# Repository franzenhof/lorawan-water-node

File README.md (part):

# LoRaWAN Water Node – Spring & Reservoir Monitor (Heltec WiFi LoRa V3)

Firmware for a custom-built PCB based on the **Heltec WiFi LoRa 32 V3** (ESP32-S3).  
The node measures flow rate, water level, and process temperatures at a natural spring or water reservoir, and transmits all data via **LoRaWAN (OTAA, region configurable; default: EU868)** to a ChirpStack server. The BME280 values are used mainly for enclosure health monitoring (humidity ingress + electronics thermal state), not as a primary water-process sensor.

---

## Project Photos

<p align="center">
     <sub><strong>Overview:</strong> Complete field setup</sub><br/>
     <sub><strong>PCB Prototype:</strong> Board and wiring stage (Fritzing prototype)</sub><br/>
     <sub><strong>Grafana:</strong> Live telemetry and trends</sub>
</p>

<p align="center">

     <br/>
     
</p>

<p align="center">
     <sub><strong>PCB v1.0 (KiCad render):</strong> top side with Heltec module footprint, bottom side with terminal labels, 3D view</sub>
</p>

---

## Quick Navigation

- [Use Case](#use-case)
- [Operating Modes & Display](#operating-modes--display)
- [Hardware](#hardware) · [PCB v1.0](#pcb-v10) · [Prototype](#prototype-fritzing)
- [GPIO Pinout](#gpio-pinout)
- [CayenneLPP Payload](#cayennelpp-payload-channels) · [Payload Format](#payload-format-cayennelpp-or-compact-binary) · [Daily Uplink](#daily-uplink-port-2)
- [Building & Flashing](#building--flashing) · [Tests](#tests)
- [Initial Configuration](#initial-configuration-wifi-portal)
- [User Button](#user-button-gpio-0)
- [Firmware Update (OTA)](#firmware-update-via-wi-fi-portal-ota)
- [LoRaWAN Session & Join](#lorawan-session--join)
- [TTN Instead of ChirpStack](#ttn-the-things-stack-instead-of-private-chirpstack)
- [Downlink Commands](#downlink-commands)
- [4–20 mA Measurement](#420-ma-current-measurement)
- [Power Saving](#power-saving-measures) · [Power Consumption](#power-consumption)
- [Libraries](#libraries)
- [ChirpStack Decoder](#chirpstack-decoder)
- [Troubleshooting](#troubleshooting)
- [Project Structure](#project-structure)
- [Changelog](#changelog)

---

## 📄 License & Open Source

This project is fully open-source. To support both software developers and hardware makers, it is dual-licensed:

* **Software / Firmware:** Licensed under the **[MIT License](LICENSE-SOFTWARE)**. You can freely use, modify, and distribute the code.
* **Hardware (Schematics, PCB & 3D Files):** Licensed under the **[CERN-OHL-P v2](LICENSE-HARDWARE)** (CERN Open Hardware Licence – Permissive). You are free to manufacture, modify, and distribute the hardware designs.

*Developed with 🚜 and 💻 by Gerhard Massenbichler at Franzenhof.*

## Use Case

```
[LiFePO4 4s] ──► [Victron MPPT] ──► charge battery
                                         │
                              [DALY Smart BMS] (protection)
                                         │ 12 V (VIN 6–33 V)
                              [Water Node PCB v1.0]
                               on-board VIN → 5 V buck, 5 V → 22 V boost
                                         │
                              [Heltec WiFi LoRa V3]
                                    │        │
               [Flow sensor, e.g. ZJ-B5]   [DS18B20 x3]
                          [4-20mA Level]   [BME280 enclosure monitor]
                          [Victron VE.Direct]
                          [DALY BMS UART]
                                    │
                               [LoRaWAN]
                                    │
                            [ChirpStack Server]
```

Every 5 minutes the node wakes from deep sleep, samples for up to 15 seconds (averaging), and sends a LoRaWAN uplink. It then returns to deep sleep. The DALY BMS is read less frequently (configurable interval, default every 6th cycle = 30 minutes).

---

## Operating Modes & Display

**Deep-sleep mode (`sleepSec > 0`, default):** wake, measure for the sampling window, send, sleep. The window ends early (after at least 5 s) once Victron and DALY have answered. The flow sensor is unpowered while sleeping, so the flow *rate* is measured during the window only.

**Continuous mode (`sleepSec = 0`):** deep sleep is disabled. The node stays awake, samples continuously over the continuous uplink interval, forms window averages, and sends at that interval. Flow, 4–20 mA level, DS18B20, BME280, and Victron V/P/I are averaged across the whole window. Flow pulses are captured without gaps (including during uplink/processing phases), so no liters are lost between cycles.
> **Note:** In continuous mode, the sampling window (`samplingMs`) is ignored — the measurement window is governed solely by the continuous interval (`continuousSendSec`).

**Display power management (automatic, no configuration needed in deep-sleep mode):**
- **Deep sleep (`sleepSec>0`):** the display is **off** on a normal timer wakeup (silent, unattended cycle), and automatically turned **on** for a fresh power-on boot or an EXT0 button wakeup — staying on until the measurement is done and the uplink has been sent, then switching off again before the next deep sleep. This is fixed behavior and not user-configurable, since keeping the display on during unattended timer cycles would only waste battery power for no benefit.
- **Continuous mode (`sleepSec=0`):** since the node never deep-sleeps, there is no wakeup event to hook into. Instead, the display stays on for `displayOnCycles` measurement cycles (configurable, default 5; **`0` = always on, no auto-off**) after boot or after a **short press** of the user button (GPIO 0), then turns off automatically until the button is pressed again. A short press is recognized even while a (potentially long) measurement window is running, so the display reacts immediately rather than waiting for the next full cycle.

If the display is on, it doesn't just show a static "Measuring..." message: it updates once per second during the whole measurement window with a countdown, the running flow rate, the running 4–20 mA level average, Victron/DALY BMS reception status (`...` while waiting, `OK` once received), and — in continuous mode — the live DS18B20 temperatures. To keep the ~750 ms 12-bit conversion from stalling the ADC/serial sampling, the DS18B20 are read **asynchronously** in continuous mode (a fresh conversion is started right after each read). At uplink time, the continuous-mode payload uses the window averages (instead of last-sample values) for flow, level, DS18B20, BME280, and Victron V/P/I. In deep-sleep mode the sensors are read once (blocking) after the short measurement window to save power. So the user always sees live feedback instead of a frozen screen.

All measurement screens (live "Measuring…", the final results screen, and the "Sending uplink…" screen) list values in a fixed **priority order (most important first): Flow → DS18B20 temperatures → Level → BME280 → Victron → DALY → rest (VIN, inputs/outputs)**. Lines are drawn compactly (only present sensors); on the 64 px panel the lowest-priority values drop off the bottom first if everything is enabled at once. The "Sending uplink…" screen keeps the measured values visible under the header instead of blanking the screen. If known and `debugMode = 1`, RF quality values (last downlink RSSI/SNR and LinkCheck results) are shown as commissioning info. When the display is off, the node does not wait at the end of the cycle (the 4 s result screen is only shown with the display on).

---

## Hardware

The hardware is **PCB v1.0** (KiCad, SMD, JLCPCB-ready) in [`pcb/v1.0/`](pcb/v1.0/). The original Fritzing board (THT, external DC-DC converters) is kept as the [prototype](#prototype-fritzing) in [`pcb/prototype/`](pcb/prototype/); the current firmware no longer supports it.

| Component | Function |
|-----------|----------|
| Heltec WiFi LoRa 32 V3 | Microcontroller (ESP32-S3), LoRa SX1262 — plugs onto the PCB (2 × 18-pin sockets), USB-C at the board edge |
| Flow sensor (open collector) | any flow sensor with open-collector output (e.g. ZJ-B5) |
| DS18B20 × 3 | 1-Wire temperature sensors (spring, tank floor, air) |
| BME280 | Enclosure health monitoring: humidity ingress indicator, enclosure/electronics temperature trend, plus barometric pressure as an additional byproduct value (I²C) |
| 4–20 mA level sensor | Two-wire loop sensor, supplied with 22 V by the on-board boost converter |
| Victron MPPT | Solar charge controller, read via VE.Direct (serial) |
| DALY Smart BMS | Battery protection, read via UART |

### PCB v1.0

**Board:** 100 × 100 mm, 2 layers, 4 × M3 mounting holes (4 mm from the edges → **92 × 80 mm** hole pattern; the lower pair sits above the terminal row). The field connectors are 3.5 mm screw terminals along the bottom edge; the I/O block (switched outputs, digital and analog inputs) sits at the top edge. The Heltec module (WiFi LoRa 32 **V3.2**, pin-compatible with V3/V3.1) plugs in at the left edge; its USB-C connector sits 1.5 mm inside the board edge (it does not protrude — updates normally go over the air). Board version and `franzenhof.com` are printed on both sides. The top silkscreen names every terminal block **and each of its pins** right at the terminal, so the board can be wired when it is mounted; it also documents the jumpers and headers. The bottom silkscreen repeats the pin names.

**RTC pin map:** every input, pulse input and output sits on an RTC GPIO (GPIO1–7, GPIO19). Inputs can therefore wake the ESP32-S3 from deep sleep (once JP9 / JP10 keep their input stage powered), and the outputs are held per pin through deep sleep.

**Power:** a single input **VIN 6–33 V** feeds everything — 4s/8s LiFePO4, 12 V / 24 V lead-acid (also 12s with equalization ≤ 33 V), 12 V or 24 V power supplies (24 V PLC supplies per IEC 61131-2):

| Block | Parts | Notes |
|---|---|---|
| Input protection | PTC F1 (1.1 A, 60 V) → bidirectional TVS **SMBJ33CA** → reverse-polarity diode SS210 (100 V) | reverse polarity is blocked by SS210 (electronics) and Q12 (outputs); the bidirectional TVS stays off, so nothing has to blow (a battery would drive far more than F1's 40 A rating into a unidirectional TVS) |
| VIN → 5 V | TI **LMR36510** synchronous buck (4.2–65 V, 1 A, 26 µA Iq) → jumper **JP8** → 5 V rail | supplies the Heltec 5 V pin |
| 5 V → 22 V | **MT3608** boost (22.2 V, below the 24 V standoff of TVS D8 with feedback tolerance), input switched by P-MOSFET AO3401A (GPIO47) | 4–20 mA loop supply, independent of VIN (also on USB power); completely off in deep sleep |
| 3.3 V | own LDO **XC6206P332MR** (U15, 200 mA, ≈ 1 µA Iq) from the 5 V rail via PTC F2; switched sensor rail via **AO3401A** (GPIO38) | the Heltec 3V3 regulator only supplies the module; the switched rail also powers the whole I²C domain (BME280, ADS1115, J16) |
| 5 V sensor rail | AO3400A + AO3401A, enabled together with the 3.3 V sensor rail | pulse sensors |
| Output load supply | own branch: VIN terminal → reverse-polarity P-MOSFET **NCE60P50K** (Q12, 60 V, 28 mΩ; D37 12 V gate clamp, R63 1 MΩ) → **eFuse TPS16630** (U16, 60 V, 31 mΩ) → J17 "+VIN" | loads run at the VIN voltage and do not stress the electronics' input fuse; no diode drop or diode heat at 3 A. U16 limits the total load current to **5.4 A** (R64 3.3k; the datasheet allows 0.6–6 A, R_ILIM ≥ 3 kΩ), so pumps and motors with a start current of up to 5.4 A start normally; above that it holds the current for at most 162 ms (less if it reaches thermal shutdown), switches off and retries every 0.65 s. On a hard short (at an output or at +VIN) it switches off within ~1 µs. The continuous rating stays 3 A in total; the eFuse protects against shorts and stalled motors, not against a moderate continuous overload between 3 and 5.4 A. It is only enabled while at least one output is on (SHDN = diode OR of the three output GPIOs, D38/D39 + R65): 21 µA with all outputs off, 1.4 mA while an output is on |

> **USB-only bench test / flashing:** remove jumper **JP8** ("5V BUCK", note printed on the bottom side). The board then runs from the Heltec USB-C port alone (ESP32, LoRa, display, sensors, inputs, ADS1115, 4–20 mA loop); only the outputs at J17 need VIN. With JP8 removed the buck converter is not back-fed, and USB and buck never drive the 5 V rail at the same time — Heltec specifies that only one supply (USB *or* 5 V pin) may be connected. Put JP8 back for normal operation.

**Field connectors** (bottom edge, left → right; function and pin names on the top silkscreen, pin names also on the bottom):

| Ref | Connector | Pins |
|---|---|---|
| J3 | VIN 6–33 V | 1 VIN, 2 GND |
| J7 | 4–20 mA level | 1 `+22V` (loop supply), 2 `SIG` (loop return → 120 Ω shunt → ADS1115) |
| J4 | Pulse inputs | 1 OC1 (flow sensor, GPIO5), 2 OC2 (2nd pulse input, GPIO6), 3 +5 V, 4 GND — **OC1/OC2 0–33 V**: open collector / NPN, contacts, 3.3/5 V logic, sensors with an internal 5 V pull-up and 12/24 V push-pull pulse outputs; PNP outputs with JP16 set to pull-down |
| J8 | 1-Wire (DS18B20) | 1 GND, 2 3V3, 3 DQ |
| J9 / J12 | VE.Direct (isolated) | screw terminal: 1 GND, 2 RX (to Victron), 3 TX (from Victron), 4 V+ — wire 1:1 to the Victron socket · **J12** JST-PH 4-pin for the **original (crossed) Victron VE.Direct cable** |
| J10 / J13 | DALY BMS UART (isolated) | 1 GND, 2 3.3 V, 3 BAT (battery voltage from the BMS port, see JP4), 4 S1 (wake-up), 5 TX (from BMS), 6 RX (to BMS) — same order as the DALY UART port · **J13** 6-pin 2.0 mm header for the original DALY cable |

**I/O block** (top edge, left → right):

| Ref | Connector | Pins / function |
|---|---|---|
| J17 | 3 switched outputs | **+VIN \| OUT1 \| OUT2 \| OUT3 \| GND** — low-side switches AON7264E (60 V, 13 mΩ; OUT1 = GPIO19 (Q11), OUT2 = GPIO2 (Q7), OUT3 = GPIO1 (Q6), HIGH = on; gates driven with 5 V by 74AHCT1G125 buffers U14/U13/U12, so the MOSFETs are fully enhanced), load between +VIN and OUTx, **3 A per output, 3 A together continuous**; the load-supply eFuse U16 limits the total to 5.4 A (start currents of pumps / motors) and switches off on a short (auto-retry, all outputs share it), freewheel diodes for valves/pumps/relays; off at reset; the load runs at the VIN voltage (12 V or 24 V loads) |
| J18 | 3 digital + 2 analog inputs | **IN1 \| IN2 \| IN3 \| AI1 \| AI2 \| GND** — IN1–3: −33…+33 V tolerant (also a reversed 24 V source); dry contacts to GND / NPN (100 kΩ pull-up via diode), PNP sensors (100 kΩ pull-down), 3.3/5 V logic or 12/24 V signals — selected per input with JP13–JP15; bidirectional TVS SMAJ33CA, 47 kΩ + clamps, 5 ms debounce, Schmitt trigger → GPIO3 / GPIO4 / GPIO7 (inverted: input high = GPIO low). AI1/AI2: 0–10 V, 100 k / 47 k divider (input resistance 147 kΩ), TVS, clamp → ADS1115 |

**Analog inputs (ADS1115, I²C 0x48):** 16-bit ADC on the switched 3.3 V. AIN0 = VIN (100 k / 10 k divider, switched on with the sensor rail — no current in deep sleep), AIN1 = 4–20 mA shunt, AIN2/AIN3 = AI1/AI2.

**Internal headers and jumpers:**

| Ref | Function |
|---|---|
| J11 | BME280: 1 3V3S (switched), 2 GND, 3 SCL, 4 SDA |
| J16 | expansion (2.54 mm, populated), pin 1 → 8: **VIN, GND, 5V, GND, 3V3S, SDA, SCL, GPIO46** — VIN at the outer end with GND as its only neighbour, 5V between two GND pins; pins 4–7 (GND, 3V3S, SDA, SCL) take a common 4-pin I²C module directly; 3.3 V logic, unprotected |
| TP1–TP6 | test pads (1 mm holes, not populated) next to each rail: GND, VIN, 5V, 3V3, 3V3 switched, 22V loop |
| TP7, TP8 | bare SMD probe pads (top): TP7 `VLD` = load supply +VIN_LOAD behind Q12 and the eFuse U16 (≈ VIN while an output is on), TP8 `3V3B` = second switched 3.3 V rail (I²C / analog / isolators) |
| JP1 / JP2 | I²C pull-ups (two separate 2-pin headers with a free position between them, so a jumper cannot bridge SCL and SDA): JP1 = extra 4.7 kΩ on SCL, JP2 = extra 4.7 kΩ on SDA for long BME280 cables (10 kΩ are always on board) |
| JP3 | DALY isolator supply: 1-2 = 3.3 V from the BMS, 2-3 = on-board 78L33 (3.3 V like the BMS UART) |
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
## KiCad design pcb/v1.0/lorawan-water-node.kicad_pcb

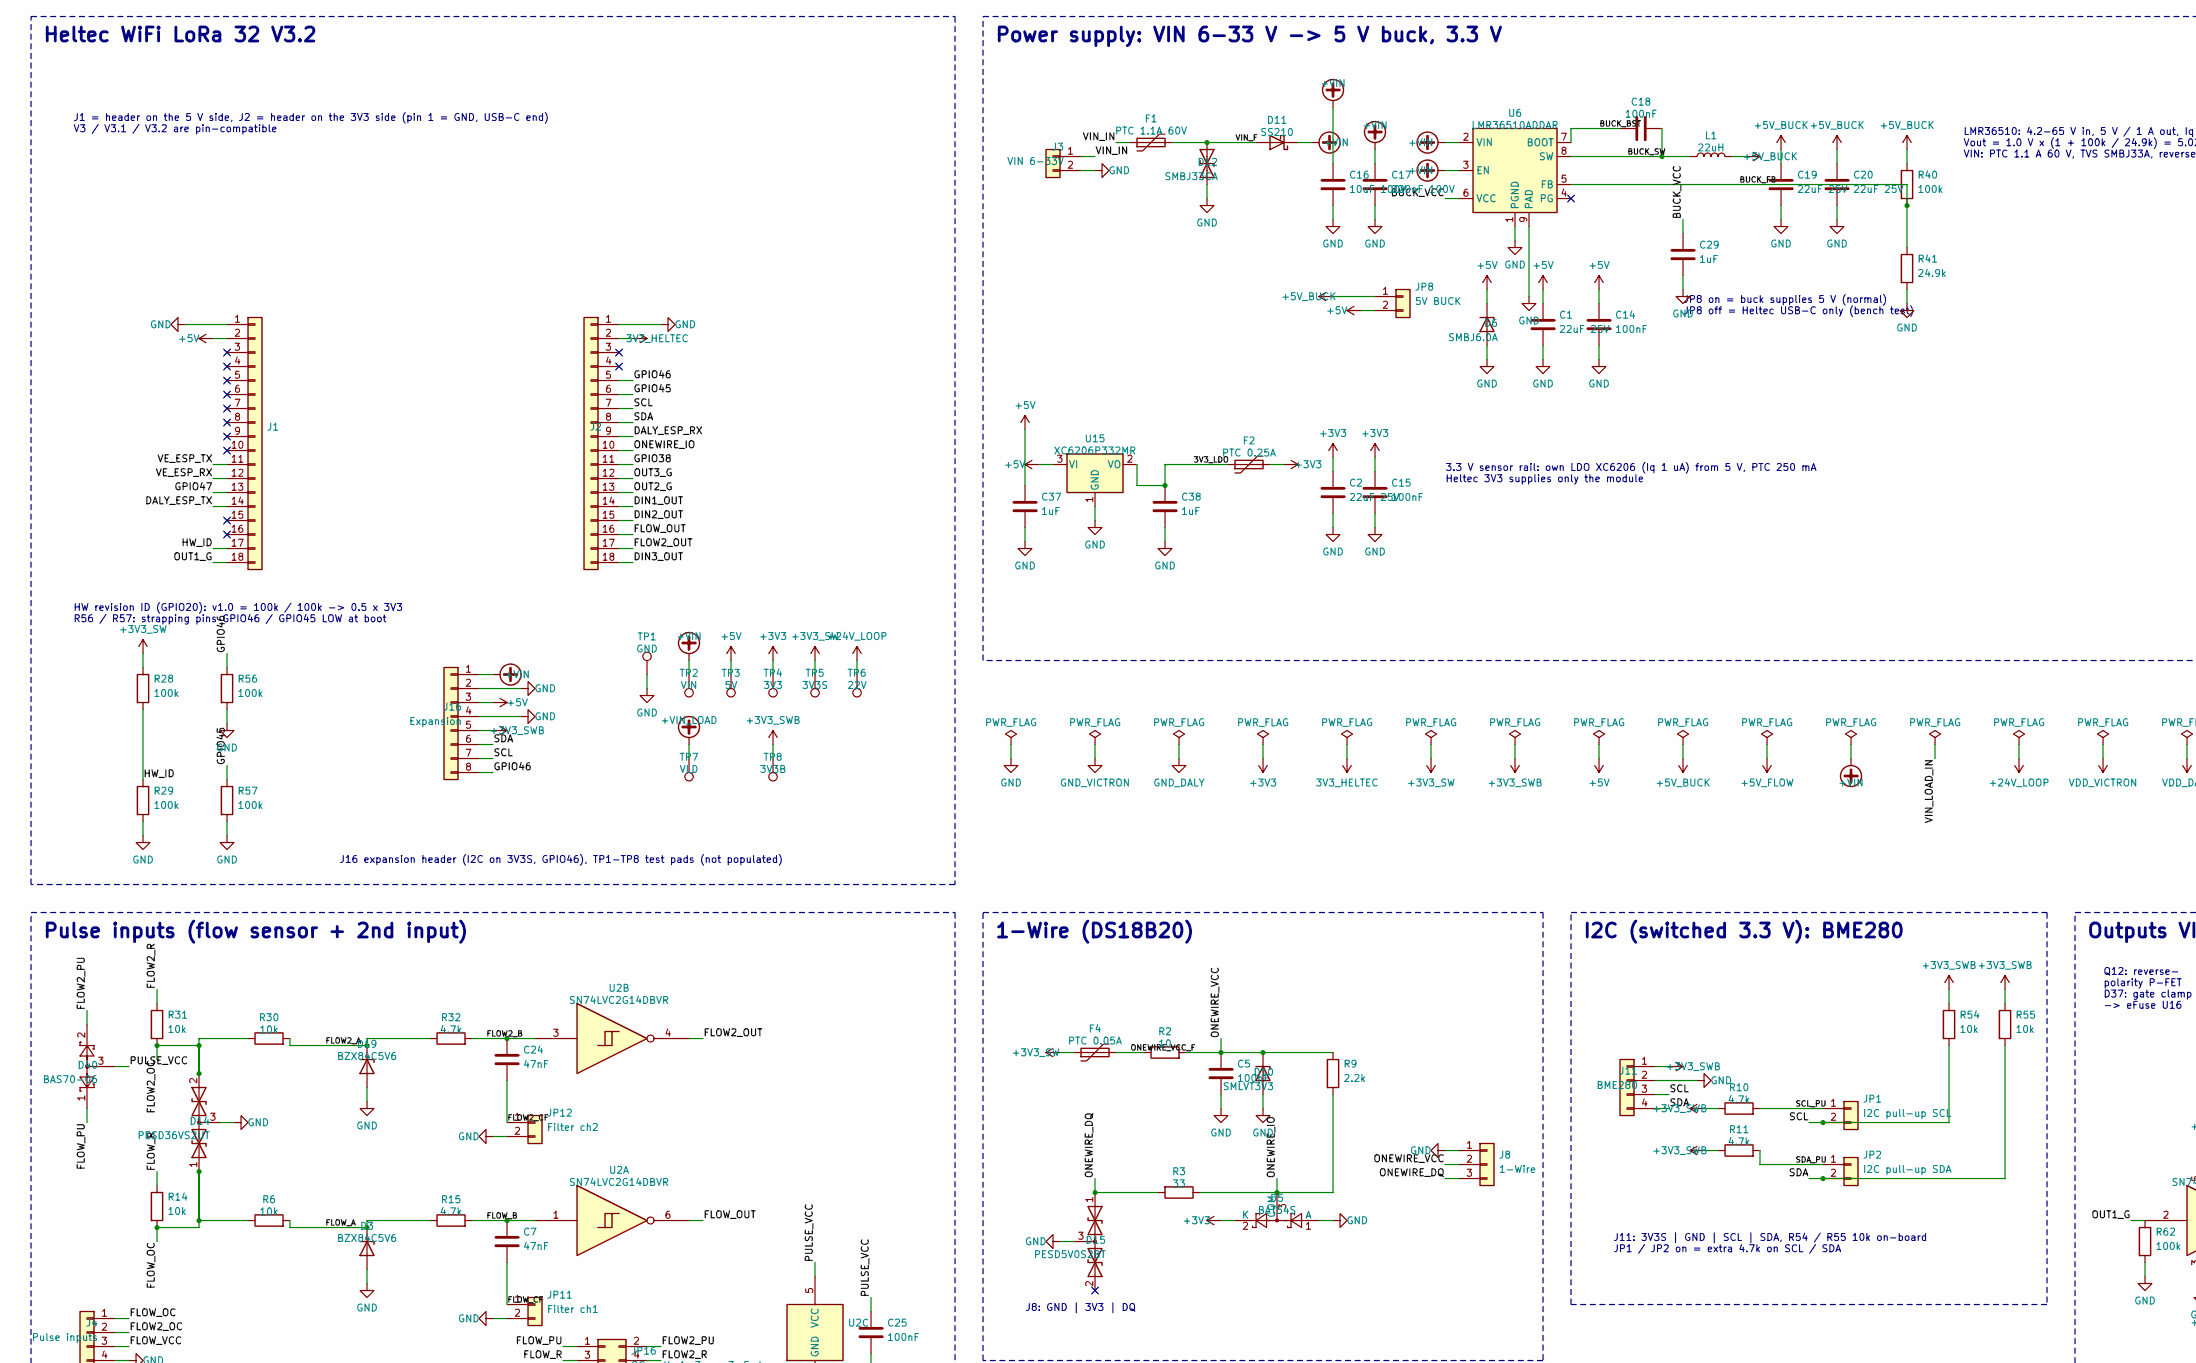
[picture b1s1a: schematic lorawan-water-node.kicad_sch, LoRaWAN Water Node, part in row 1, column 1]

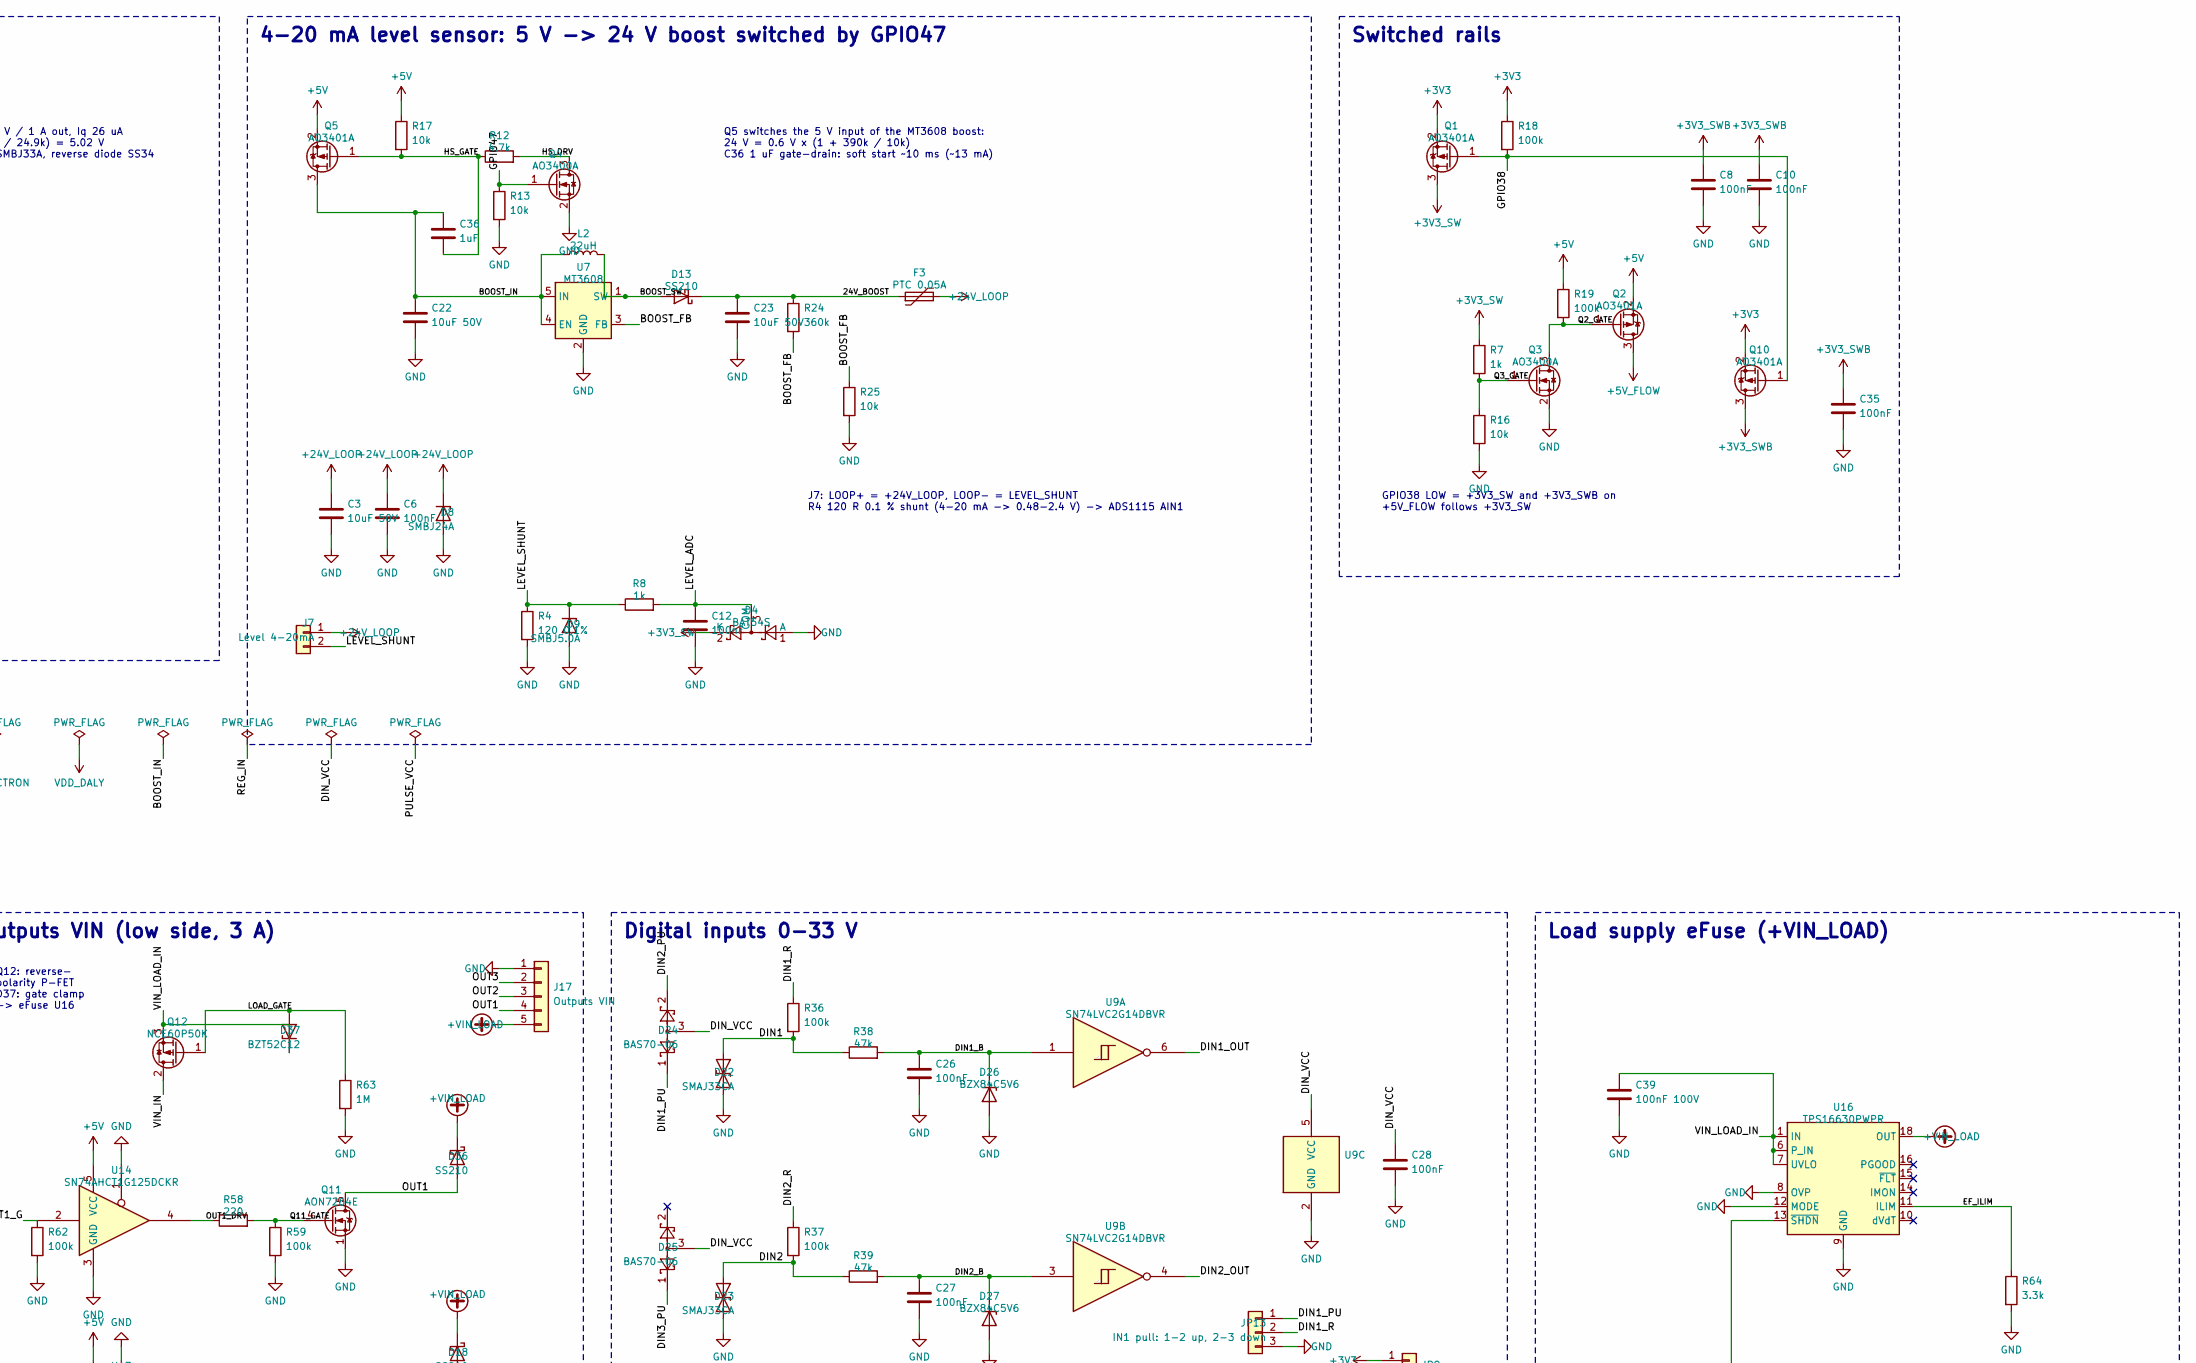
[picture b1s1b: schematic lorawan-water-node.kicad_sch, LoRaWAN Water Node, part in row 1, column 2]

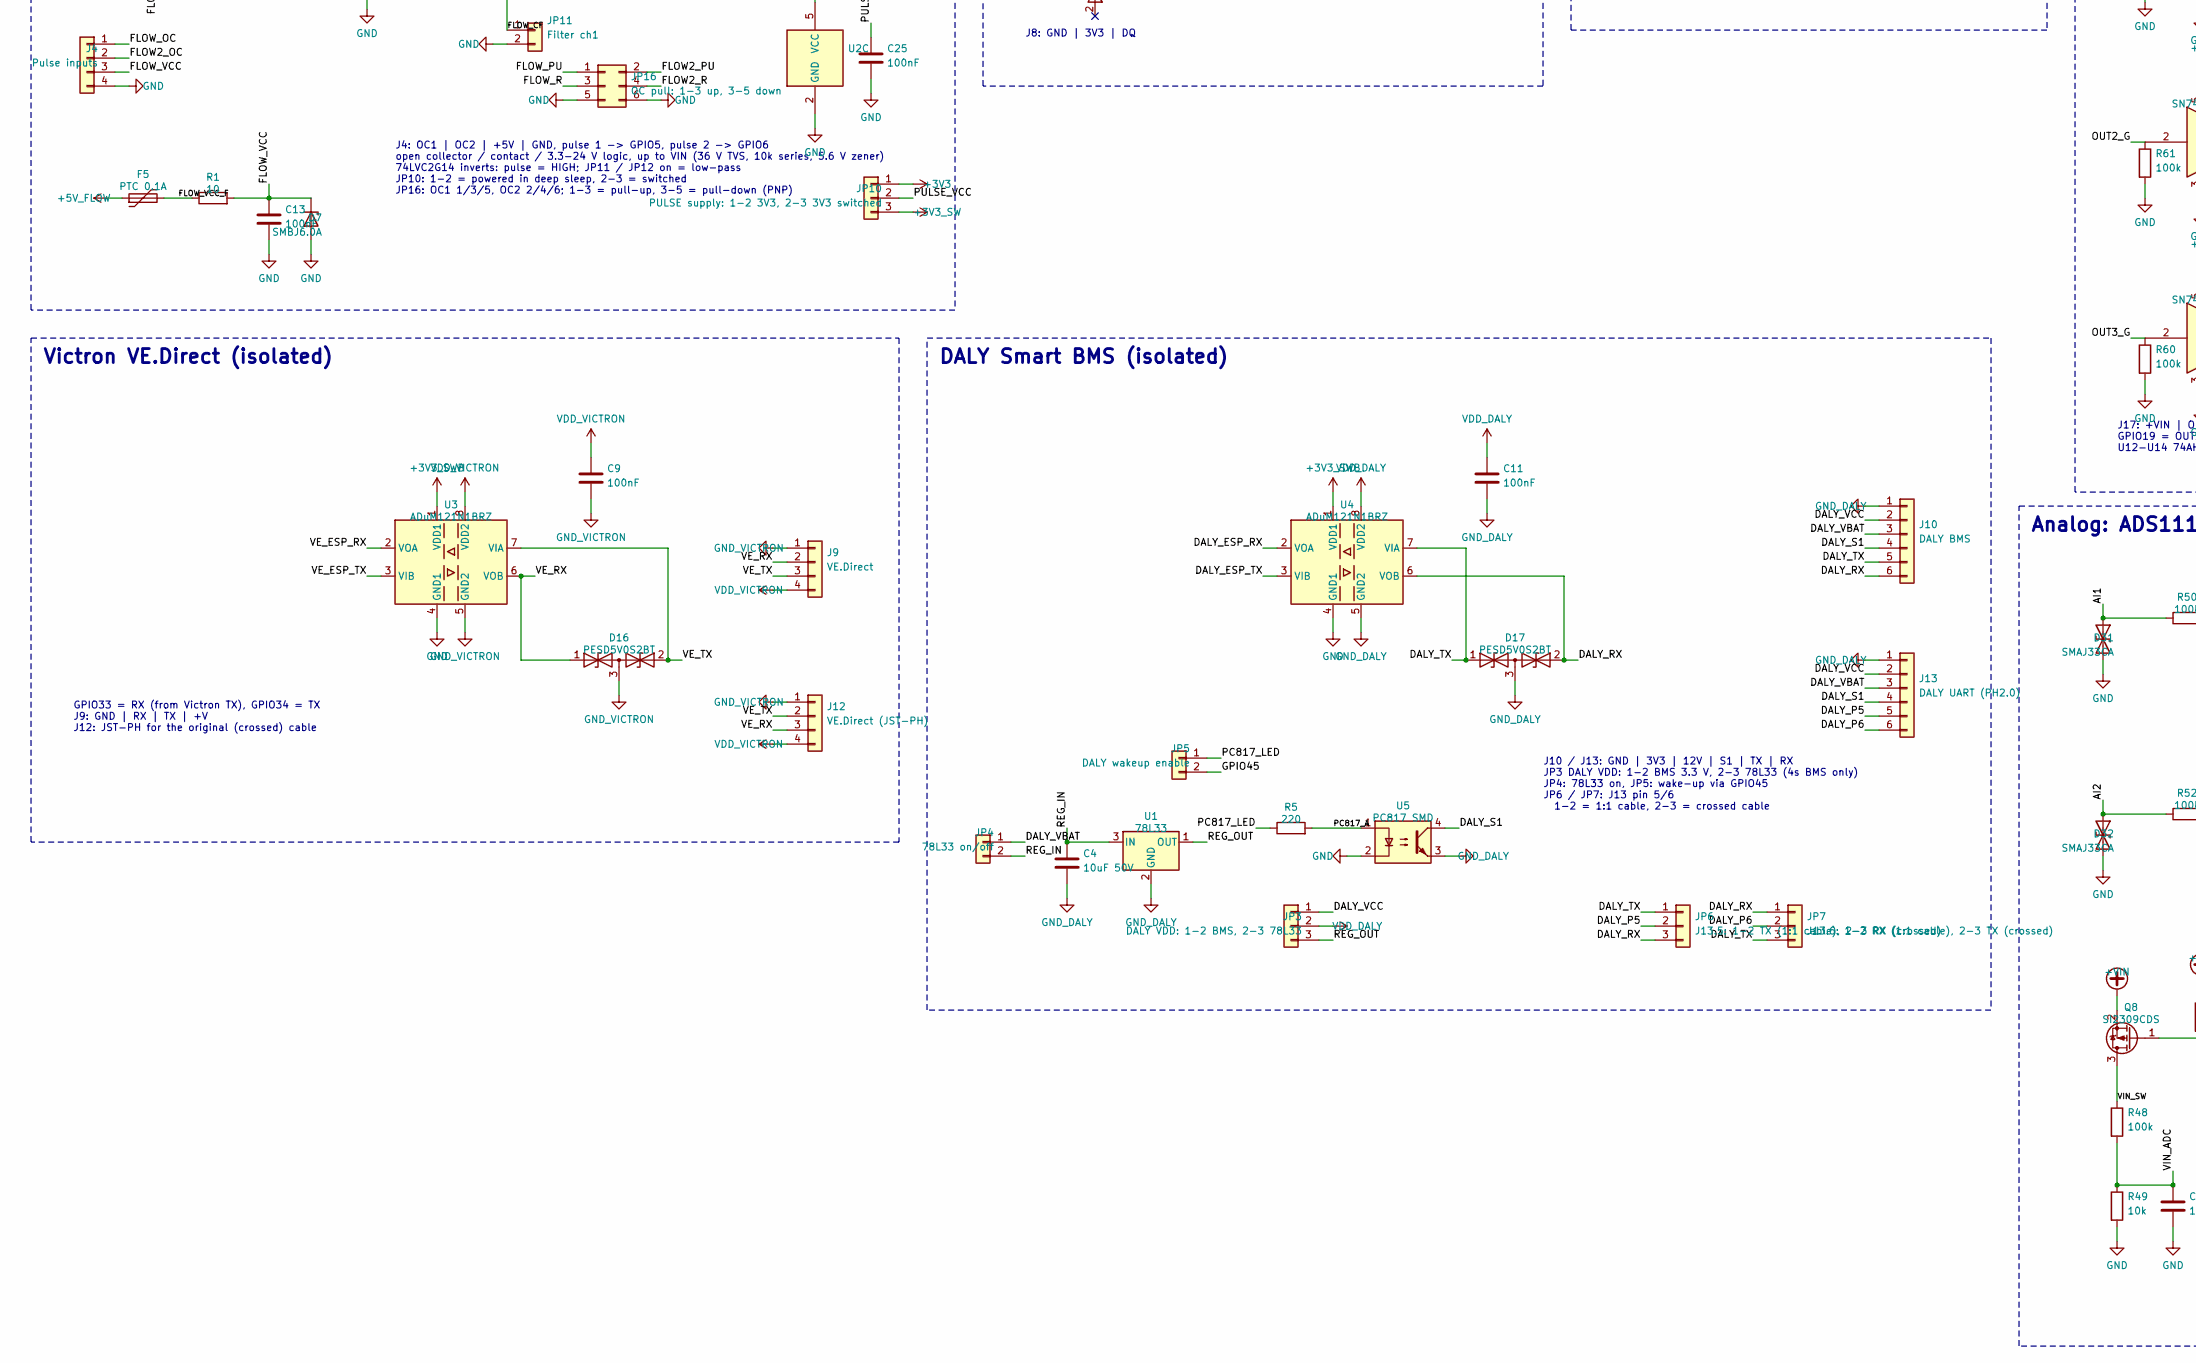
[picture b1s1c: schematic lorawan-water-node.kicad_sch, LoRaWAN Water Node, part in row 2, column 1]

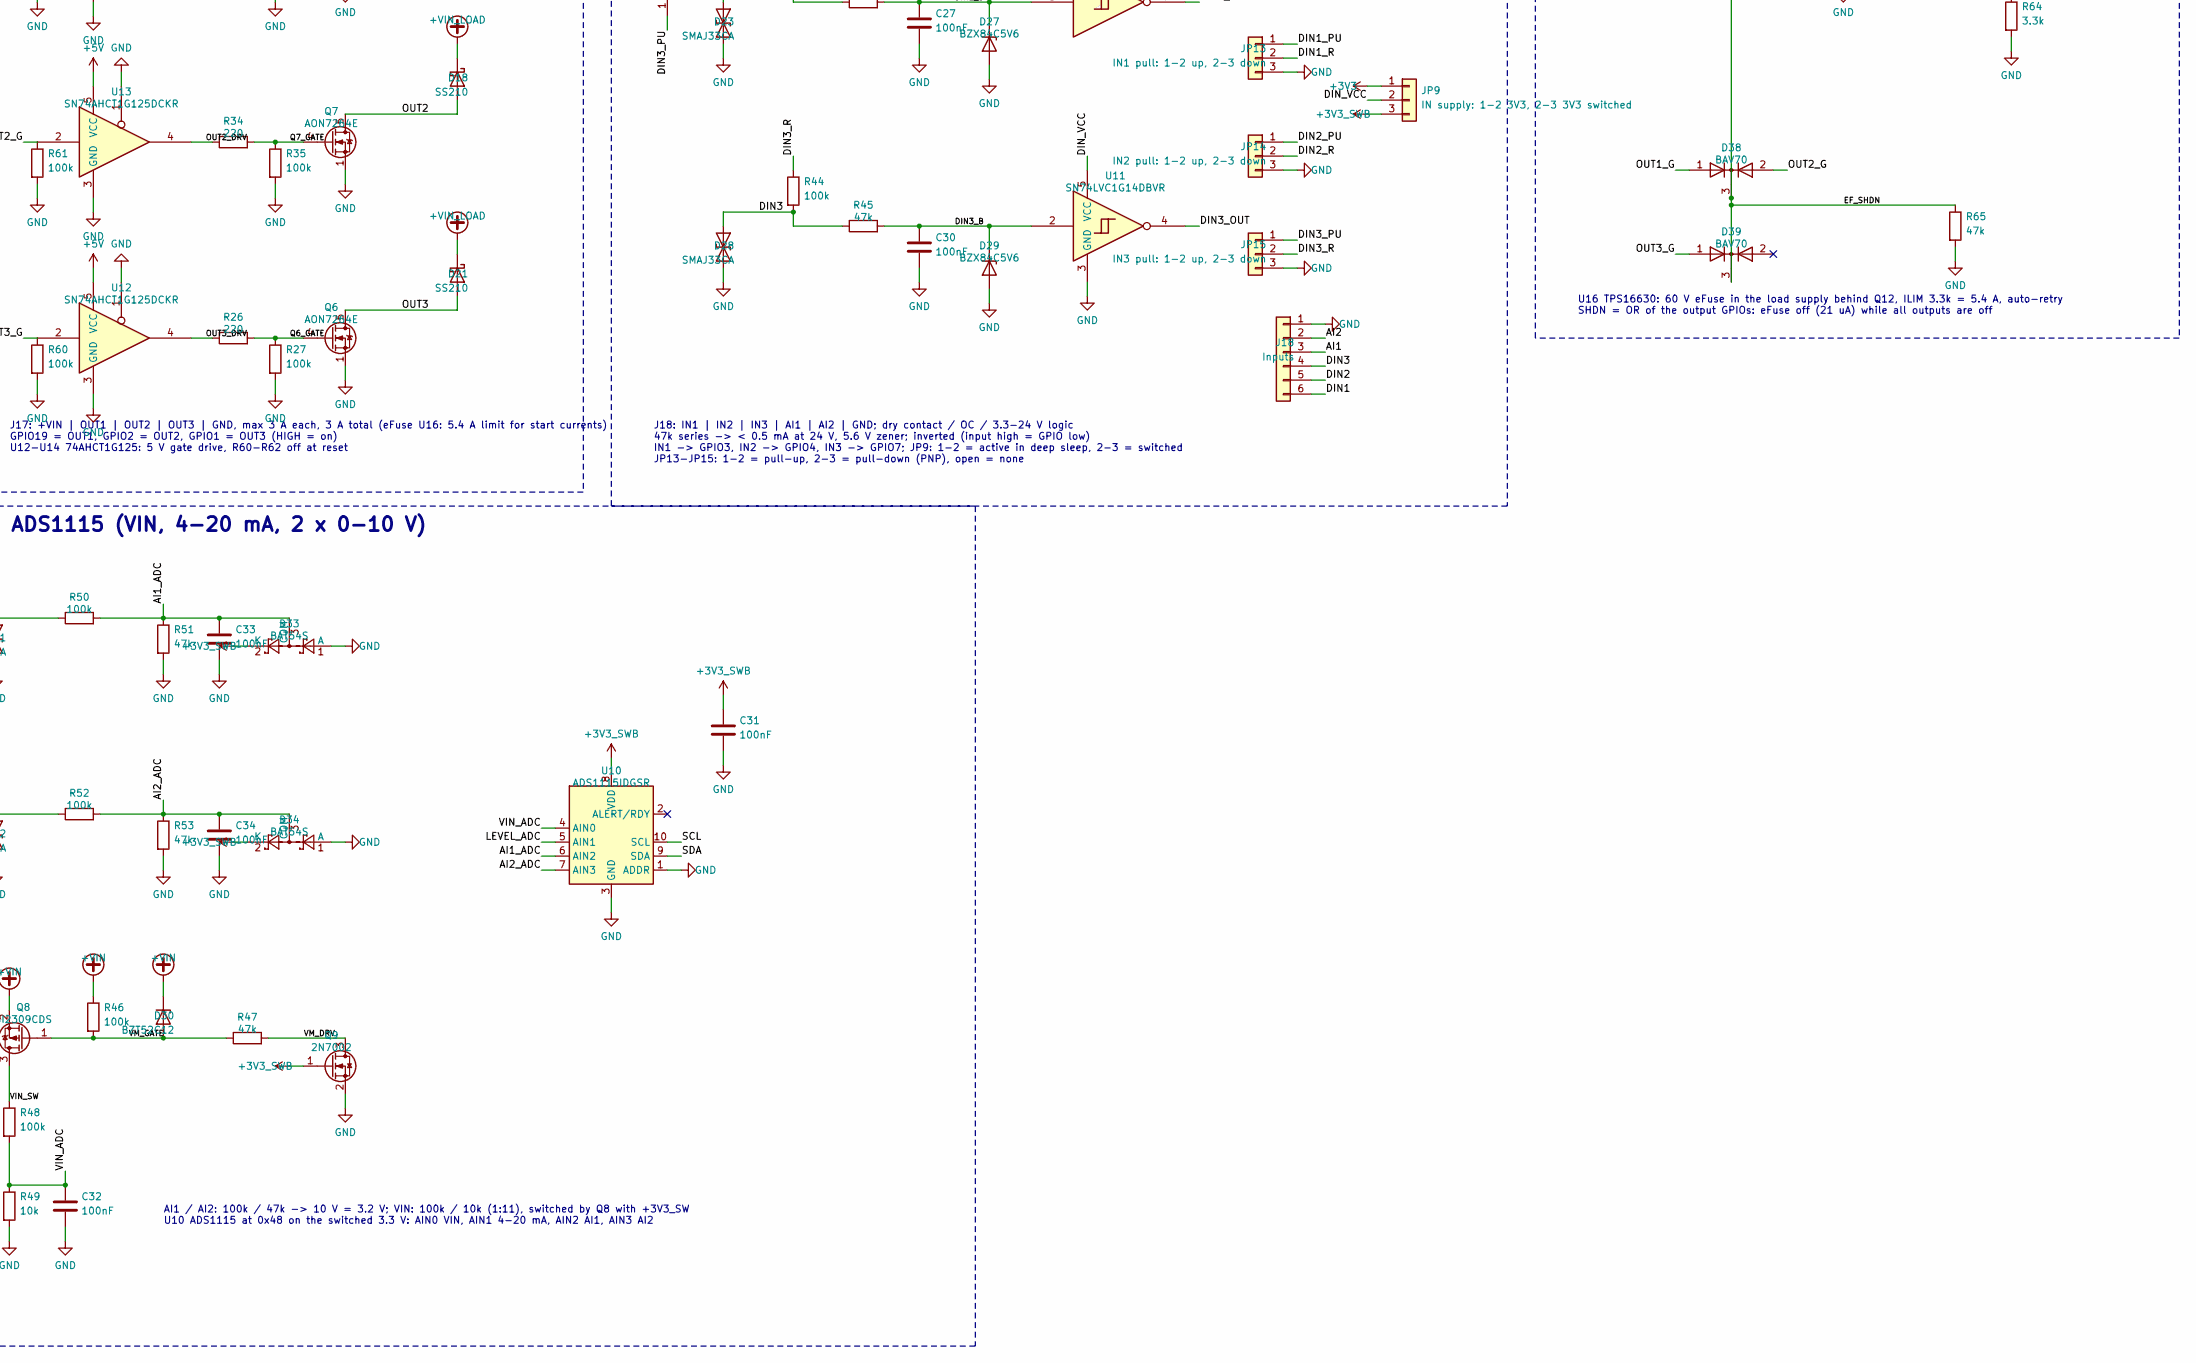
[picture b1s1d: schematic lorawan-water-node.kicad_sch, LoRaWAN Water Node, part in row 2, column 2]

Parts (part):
C1, C2, C19, C20: 22uF 25V; C_0805_2012Metric; MPN Samsung CL21A226MAQNNNE (25V X5R); LCSC C45783
C3, C4, C22, C23: 10uF 50V; C_1210_3225Metric; MPN Yageo CC1210KKX7R9BB106; LCSC C596319
C5, C6, C8, C9, C10, C11, C12, C13, C14, C15, C18, C25, C26, C27, C28, C30, C31, C32, C33, C34, C35: 100nF; C_0805_2012Metric; MPN Yageo CC0805KRX7R9BB104; LCSC C49678
C7, C24: 47nF; C_0805_2012Metric; MPN Samsung CL21B473KBCNNNC (50V X7R, basic); LCSC C53134
C16: 10uF 100V; C_1210_3225Metric; MPN FS32X106K101EGG (100V X7R 1210); LCSC C5156756
C17: 220nF 100V; C_0805_2012Metric; MPN Yageo CC0805KKX7R0BB224 (100V X7R); LCSC C513710
C29, C36, C37, C38: 1uF; C_0805_2012Metric; MPN Samsung CL21B105KBFNNNE (50V X7R); LCSC C28323
C39: 100nF 100V; C_0805_2012Metric; MPN Samsung CL21B104KCFNNNE (100V X7R); LCSC C28233
D3, D19, D26, D27, D29: BZX84C5V6; SOT-23; MPN onsemi BZX84C5V6LT1G; LCSC C82471
D4, D5, D33, D34: BAT54S; SOT-23; MPN R+O BAT54S (preferred); LCSC C7420333
D6, D7: SMBJ6.0A; D_SMB; MPN SMBJ6.0A; LCSC C113976
D8: SMBJ24A; D_SMB; MPN SMBJ24A; LCSC C123819
D9: SMBJ5.0A; D_SMB; MPN SMBJ5.0A; LCSC C78423
D10: SMLVT3V3; D_SMB; MPN SMLVT3V3; LCSC C283619
D11, D13, D18, D21, D36: SS210; D_SMA; MPN SS210 (100 V 2 A Schottky, basic); LCSC C14996
D12: SMBJ33CA; D_SMB; MPN SMBJ33CA (bidirectional); LCSC C78420
D14: PESD36VS2UT; SOT-23; MPN Nexperia PESD36VS2UT,215 (36 V, 2 lines); LCSC C85381
D15, D16, D17: PESD5V0S2BT; SOT-23; MPN Nexperia PESD5V0S2BT,215; LCSC C49338
D22, D23, D28, D31, D32: SMAJ33CA; D_SMA; MPN SMAJ33CA (400 W, bidirectional); LCSC C115251
D24, D25, D40: BAS70-06; SOT-23; MPN Nexperia BAS70-06,215 (70 V Schottky, c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; LCSC C8651
D30, D37: BZT52C12; D_SOD-123; MPN BZT52C12 (preferred); LCSC C19077410
D38, D39: BAV70; SOT-23; MPN BAV70 (common cathode, basic); LCSC C68978
F1: PTC 1.1A 60V; Fuse_2920_7451Metric; MPN BHFUSE BSMD2920-100-60V; LCSC C3020148
F2: PTC 0.25A; Fuse_1206_3216Metric; MPN nSMD025 (16V); LCSC C70068
F3, F4: PTC 0.05A; Fuse_1206_3216Metric; MPN Littelfuse 1206L005/60NR (60V); LCSC C7542924
F5: PTC 0.1A; Fuse_1206_3216Metric; MPN nSMD010 (60V); LCSC C70065
J1: Heltec V3 header (5V side); PinSocket_1x18_P2.54mm_Vertical; MPN Kinghelm KH-2.54FH-1X18P-H8.5; LCSC C2905422
J2: Heltec V3 header (3V3 side); PinSocket_1x18_P2.54mm_Vertical; MPN Kinghelm KH-2.54FH-1X18P-H8.5; LCSC C2905422
J3: VIN 6-33V; TerminalBlock_Phoenix_PT-1,5-2-3.5-H_1x02_P3.50mm_Horizontal; MPN DB125-3.5-2P-GN-S; LCSC C466970
J4: Pulse inputs; TerminalBlock_Phoenix_PT-1,5-4-3.5-H_1x04_P3.50mm_Horizontal; MPN DB125-3.5-4P-GN-S; LCSC C2757925
J7: Level 4-20mA; TerminalBlock_Phoenix_PT-1,5-2-3.5-H_1x02_P3.50mm_Horizontal; MPN DB125-3.5-2P-GN-S; LCSC C466970
J8: 1-Wire; TerminalBlock_Phoenix_PT-1,5-3-3.5-H_1x03_P3.50mm_Horizontal; MPN DB125-3.5-3P-GN-S; LCSC C466971
J9: VE.Direct; TerminalBlock_Phoenix_PT-1,5-4-3.5-H_1x04_P3.50mm_Horizontal; MPN DB125-3.5-4P-GN-S; LCSC C2757925
J10: DALY BMS; TerminalBlock_Phoenix_PT-1,5-6-3.5-H_1x06_P3.50mm_Horizontal; MPN DB125-3.5-6P-GN-S; LCSC C5290323
J11: BME280; PinHeader_1x04_P2.54mm_Vertical; MPN LXWCONN 254PZ-1x4P-V; LCSC C53055674
J12: VE.Direct (JST-PH); JST_PH_B4B-PH-K_1x04_P2.00mm_Vertical; MPN JST B4B-PH-K-S(LF)(SN); LCSC C131334
J13: DALY UART (PH2.0); JST_PH_B6B-PH-K_1x06_P2.00mm_Vertical; MPN JST B6B-PH-K-S(LF)(SN); LCSC C131342
J16: Expansion; PinHeader_1x08_P2.54mm_Vertical; MPN HX PZ2.54-1x8P ZZ; LCSC C32713274
J17: Outputs VIN; TerminalBlock_Phoenix_PT-1,5-5-3.5-H_1x05_P3.50mm_Horizontal; MPN DB125-3.5-5P-GN-S; LCSC C3646874
J18: Inputs; TerminalBlock_Phoenix_PT-1,5-6-3.5-H_1x06_P3.50mm_Horizontal; MPN DB125-3.5-6P-GN-S; LCSC C5290323
JP1: I2C pull-up SCL; PinHeader_1x02_P2.54mm_Vertical; MPN LXWCONN 254PZ-1x2P-V; LCSC C53055672
JP2: I2C pull-up SDA; PinHeader_1x02_P2.54mm_Vertical; MPN LXWCONN 254PZ-1x2P-V; LCSC C53055672
JP3: DALY VDD: 1-2 BMS, 2-3 78L33; PinHeader_1x03_P2.54mm_Vertical; MPN BOOMELE 2.54-1*3P; LCSC C49257
JP4: 78L33 on/off; PinHeader_1x02_P2.54mm_Vertical; MPN LXWCONN 254PZ-1x2P-V; LCSC C53055672
JP5: DALY wakeup enable; PinHeader_1x02_P2.54mm_Vertical; MPN LXWCONN 254PZ-1x2P-V; LCSC C53055672
JP6: J13.5: 1-2 TX (1:1 cable), 2-3 RX (crossed); PinHeader_1x03_P2.54mm_Vertical; MPN BOOMELE 2.54-1*3P; LCSC C49257
JP7: J13.6: 1-2 RX (1:1 cable), 2-3 TX (crossed); PinHeader_1x03_P2.54mm_Vertical; MPN BOOMELE 2.54-1*3P; LCSC C49257
JP8: 5V BUCK; PinHeader_1x02_P2.54mm_Vertical; MPN LXWCONN 254PZ-1x2P-V; LCSC C53055672
JP9: IN supply: 1-2 3V3, 2-3 3V3 switched; PinHeader_1x03_P2.54mm_Vertical; MPN BOOMELE 2.54-1*3P; LCSC C49257
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
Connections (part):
3V3_HELTEC: J2.2
+3V3: C2.1, C15.1, D5.2 (K), F2.2, JP9.1, JP10.1, Q1.2 (S), Q10.2 (S), R18.1, TP4.1
+3V3_SW: D4.2 (K), F4.1, JP10.3, Q1.3 (D), R7.1, R28.1, TP5.1
+3V3_SWB: C8.1, C10.1, C31.1, C35.1, D33.2 (K), D34.2 (K), J11.1, J16.5, JP9.3, Q9.1 (G), Q10.3 (D), R10.1, R11.1, R54.1, R55.1, TP8.1, U3.1 (VDD1), U4.1 (VDD1), U10.8 (VDD)
+5V: C1.1, C14.1, C37.1, D6.1 (K), J1.2, J16.3, JP8.2, Q2.2 (S), Q5.2 (S), R17.1, R19.1, TP3.1, U12.5 (VCC), U13.5 (VCC), U14.5 (VCC), U15.3 (VI)
+5V_BUCK: C19.1, C20.1, JP8.1, L1.2, R40.1
+5V_FLOW: F5.1, Q2.3 (D)
+24V_LOOP: C3.1, C6.1, D8.1 (K), F3.2, J7.1, TP6.1
+VIN: C16.1, C17.1, D11.1 (K), D30.1 (K), J16.1, Q8.2 (S), R46.1, TP2.1, U6.2 (VIN), U6.3 (EN)
+VIN_LOAD: D18.1 (K), D21.1 (K), D36.1 (K), J17.5, TP7.1, U16.18 (OUT), U16.19 (OUT), U16.20 (OUT)
/3V3_LDO: C38.1, F2.1, U15.2 (VO)
/24V_BOOST: C23.1, D13.1 (K), F3.1, R24.1
/AI1: D31.1 (A1), J18.3, R50.1
/AI1_ADC: C33.1, D33.3 (COM), R50.2, R51.1, U10.6 (AIN2)
/AI2: D32.1 (A1), J18.2, R52.1
/AI2_ADC: C34.1, D34.3 (COM), R52.2, R53.1, U10.7 (AIN3)
/BOOST_FB: R24.2, R25.1, U7.3 (FB)
/BOOST_IN: C22.1, C36.1, L2.1, Q5.3 (D), U7.4 (EN), U7.5 (IN)
/BOOST_SW: D13.2 (A), L2.2, U7.1 (SW)
/BUCK_BST: C18.1, U6.7 (BOOT)
/BUCK_FB: R40.2, R41.1, U6.5 (FB)
/BUCK_SW: C18.2, L1.1, U6.8 (SW)
/BUCK_VCC: C29.1, U6.6 (VCC)
/DALY_ESP_RX: J2.9, U4.2 (VOA)
/DALY_ESP_TX: J1.14, U4.3 (VIB)
/DALY_P5: J13.5, JP6.2
/DALY_P6: J13.6, JP7.2
/DALY_RX: D17.2 (A2), J10.6, JP6.3, JP7.1, U4.6 (VOB)
/DALY_S1: J10.4, J13.4, U5.4
/DALY_TX: D17.1 (A1), J10.5, JP6.1, JP7.3, U4.7 (VIA)
/DALY_VBAT: J10.3, J13.3, JP4.1
/DALY_VCC: J10.2, J13.2, JP3.1
/DIN1: D22.1 (A1), J18.6, R36.2, R38.1
/DIN1_B: C26.1, D26.3 (K), R38.2, U9.1
/DIN1_OUT: J2.14, U9.6
/DIN1_PU: D24.1, JP13.1
/DIN1_R: JP13.2, R36.1
/DIN2: D23.1 (A1), J18.5, R37.2, R39.1
/DIN2_B: C27.1, D27.3 (K), R39.2, U9.3
/DIN2_OUT: J2.15, U9.4
/DIN2_PU: D24.2, JP14.1
/DIN2_R: JP14.2, R37.1
/DIN3: D28.1 (A1), J18.4, R44.2, R45.1
/DIN3_B: C30.1, D29.3 (K), R45.2, U11.2
/DIN3_OUT: J2.18, U11.4
/DIN3_PU: D25.1, JP15.1
/DIN3_R: JP15.2, R44.1
/DIN_VCC: C28.1, D24.3, D25.3, JP9.2, U9.5 (VCC), U11.5 (VCC)
/EF_SHDN: D38.3 (K), D39.3 (K), R65.1, U16.13 (~SHDN)
/FLOW2_A: D19.3 (K), R30.2, R32.1
/FLOW2_B: C24.1, R32.2, U2.3
/FLOW2_CF: C24.2, JP12.1
/FLOW2_OC: D14.2 (A2), J4.2, R30.1, R31.2
/FLOW2_OUT: J2.17, U2.4
/FLOW2_PU: D40.2, JP16.2
/FLOW2_R: JP16.4, R31.1
/FLOW_A: D3.3 (K), R6.2, R15.1
/FLOW_B: C7.1, R15.2, U2.1
/FLOW_CF: C7.2, JP11.1
/FLOW_OC: D14.1 (A1), J4.1, R6.1, R14.2
/FLOW_OUT: J2.16, U2.6
/FLOW_PU: D40.1, JP16.1
/FLOW_R: JP16.3, R14.1
/FLOW_VCC: C13.1, D7.1 (K), J4.3, R1.2
/FLOW_VCC_F: F5.2, R1.1
/GPIO38: J2.11, Q1.1 (G), Q10.1 (G), R18.2
/GPIO45: J2.6, JP5.2, R57.1
/GPIO46: J2.5, J16.8, R56.1
/GPIO47: J1.13, Q4.1 (G), R13.1
/HS_DRV: Q4.3 (D), R12.2
/HS_GATE: C36.2, Q5.1 (G), R12.1, R17.2
/HW_ID: J1.17, R28.2, R29.1
/LEVEL_ADC: C12.1, D4.3 (COM), R8.2, U10.5 (AIN1)
/LEVEL_SHUNT: D9.1 (K), J7.2, R4.1, R8.1
/LOAD_GATE: D37.2 (A), Q12.1 (G), R63.1
/ONEWIRE_DQ: D15.1 (A1), J8.3, R3.2
/ONEWIRE_IO: D5.3 (COM), J2.10, R3.1, R9.2
/ONEWIRE_VCC: C5.1, D10.1 (K), J8.2, R2.2, R9.1
/ONEWIRE_VCC_F: F4.2, R2.1
/OUT1: D36.2 (A), J17.4, Q11.5 (D)
/OUT1_DRV: R58.1, U14.4
/OUT1_G: D38.1 (A), J1.18, R62.1, U14.2
/OUT2: D18.2 (A), J17.3, Q7.5 (D)
/OUT2_DRV: R34.1, U13.4
/OUT2_G: D38.2 (A), J2.13, R61.1, U13.2
/OUT3: D21.2 (A), J17.2, Q6.5 (D)
/OUT3_DRV: R26.1, U12.4
/OUT3_G: D39.1 (A), J2.12, R60.1, U12.2
/PC817_A: R5.2, U5.1
/PC817_LED: JP5.1, R5.1
/PULSE_VCC: C25.1, D40.3, JP10.2, U2.5 (VCC)
/Q2_GATE: Q2.1 (G), Q3.3 (D), R19.2
/Q3_GATE: Q3.1 (G), R7.2, R16.1
/Q6_GATE: Q6.4 (G), R26.2, R27.1
/Q7_GATE: Q7.4 (G), R34.2, R35.1
/Q11_GATE: Q11.4 (G), R58.2, R59.1
/REG_IN: C4.1, JP4.2, U1.3 (IN)
/REG_OUT: JP3.3, U1.1 (OUT)
/SCL: J2.7, J11.3, J16.7, JP1.2, R54.2, U10.10 (SCL)
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
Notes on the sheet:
Heltec WiFi LoRa 32 V3.2
J1 = header on the 5 V side, J2 = header on the 3V3 side (pin 1 = GND, USB-C end) V3 / V3.1 / V3.2 are pin-compatible
HW revision ID (GPIO20): v1.0 = 100k / 100k -> 0.5 x 3V3 R56 / R57: strapping pins GPIO46 / GPIO45 LOW at boot
J16 expansion header (I2C on 3V3S, GPIO46), TP1-TP8 test pads (not populated)
Power supply: VIN 6-33 V -> 5 V buck, 3.3 V
LMR36510: 4.2-65 V in, 5 V / 1 A out, Iq 26 uA Vout = 1.0 V x (1 + 100k / 24.9k) = 5.02 V VIN: PTC 1.1 A 60 V, TVS SMBJ33A, reverse diode SS34
JP8 on = buck supplies 5 V (normal) JP8 off = Heltec USB-C only (bench test)
3.3 V sensor rail: own LDO XC6206 (Iq 1 uA) from 5 V, PTC 250 mA Heltec 3V3 supplies only the module
4-20 mA level sensor: 5 V -> 24 V boost switched by GPIO47
Q5 switches the 5 V input of the MT3608 boost: 24 V = 0.6 V x (1 + 390k / 10k) C36 1 uF gate-drain: soft start ~10 ms (~13 mA)
J7: LOOP+ = +24V_LOOP, LOOP- = LEVEL_SHUNT R4 120 R 0.1 % shunt (4-20 mA -> 0.48-2.4 V) -> ADS1115 AIN1
Switched rails
GPIO38 LOW = +3V3_SW and +3V3_SWB on +5V_FLOW follows +3V3_SW
Pulse inputs (flow sensor + 2nd input)
J4: OC1 | OC2 | +5V | GND, pulse 1 -> GPIO5, pulse 2 -> GPIO6 open collector / contact / 3.3-24 V logic, up to VIN (36 V TVS, 10k series, 5.6 V zener) 74LVC2G14 inverts: pulse = HIGH; JP11 / JP12 on = low-pass JP10: 1-2 = powered in deep sleep, 2-3 = switched JP16: OC1 1/3/5, OC2 2/4/6; 1-3 = pull-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
1-Wire (DS18B20)
J8: GND | 3V3 | DQ
I2C (switched 3.3 V): BME280
J11: 3V3S | GND | SCL | SDA, R54 / R55 10k on-board JP1 / JP2 on = extra 4.7k on SCL / SDA
Outputs VIN (low side, 3 A)
Q12: reverse- polarity P-FET D37: gate clamp -> eFuse U16
J17: +VIN | OUT1 | OUT2 | OUT3 | GND, max 3 A each, 3 A total (eFuse U16: 5.4 A limit for start currents) GPIO19 = OUT1, GPIO2 = OUT2, GPIO1 = OUT3 (HIGH = on) U12-U14 74AHCT1G125: 5 V gate drive, R60-R62 off at reset
Load supply eFuse (+VIN_LOAD)
U16 TPS16630: 60 V eFuse in the load supply behind Q12, ILIM 3.3k = 5.4 A, auto-retry SHDN = OR of the output GPIOs: eFuse off (21 uA) while all outputs are off
Digital inputs 0-33 V
J18: IN1 | IN2 | IN3 | AI1 | AI2 | GND; dry contact / OC / 3.3-24 V logic 47k series -> < 0.5 mA at 24 V, 5.6 V zener; inverted (input high = GPIO low) IN1 -> GPIO3, IN2 -> GPIO4, IN3 -> GPIO7; JP9: 1-2 = active in deep sleep, 2-3 = switched JP13-JP15: 1-2 = pull-up, 2-3 = pull-down (PNP), open = n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
Analog: ADS1115 (VIN, 4-20 mA, 2 x 0-10 V)
AI1 / AI2: 100k / 47k -> 10 V = 3.2 V; VIN: 100k / 10k (1:11), switched by Q8 with +3V3_SW U10 ADS1115 at 0x48 on the switched 3.3 V: AIN0 VIN, AIN1 4-20 mA, AIN2 AI1, AIN3 AI2
Victron VE.Direct (isolated)
GPIO33 = RX (from Victron TX), GPIO34 = TX J9: GND | RX | TX | +V J12: JST-PH for the original (crossed) cable
DALY Smart BMS (isolated)
J10 / J13: GND | 3V3 | 12V | S1 | TX | RX JP3 DALY VDD: 1-2 BMS 3.3 V, 2-3 78L33 (4s BMS only) JP4: 78L33 on, JP5: wake-up via GPIO45 JP6 / JP7: J13 pin 5/6 1-2 = 1:1 cable, 2-3 = crossed cable

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

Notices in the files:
pcb/v1.0/lorawan-water-node.kicad_pcb:
franzenhof.com  -  CERN-OHL-P v2
